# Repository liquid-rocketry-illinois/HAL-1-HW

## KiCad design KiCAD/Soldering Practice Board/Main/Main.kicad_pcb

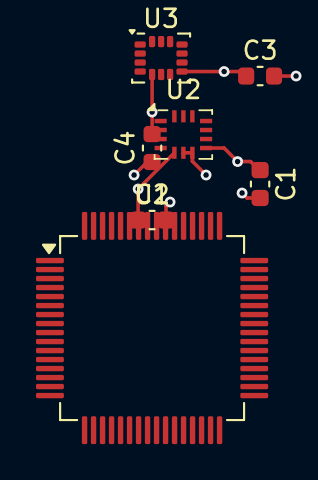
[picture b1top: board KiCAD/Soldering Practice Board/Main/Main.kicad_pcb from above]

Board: 2 copper layers, 7 parts (0 on the bottom side), 2 nets.

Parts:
C1, C2, C3, C4: 100n; C_0603_1608Metric
U1: STM32C071R8Tx; LQFP-64_10x10mm_P0.5mm
U2: BMI160; Bosch_LGA-14_3x2.5mm_P0.5mm
U3: LSM6DS3; LGA-14_3x2.5mm_P0.5mm_LayoutBorder3x4y

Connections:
+3V3: C1.1, C2.1, C3.1, C4.2, U1.7 (VREF+), U1.8 (VDD), U2.5 (VDDIO), U2.8 (VDD), U3.5 (VDDIO), U3.8 (VDD)
GND: C1.2, C2.2, C3.2, C4.1, U1.9 (VSS), U2.6 (GNDIO), U2.7 (GND), U3.2 (SDX), U3.3 (SCX), U3.6 (GND), U3.7 (GND)

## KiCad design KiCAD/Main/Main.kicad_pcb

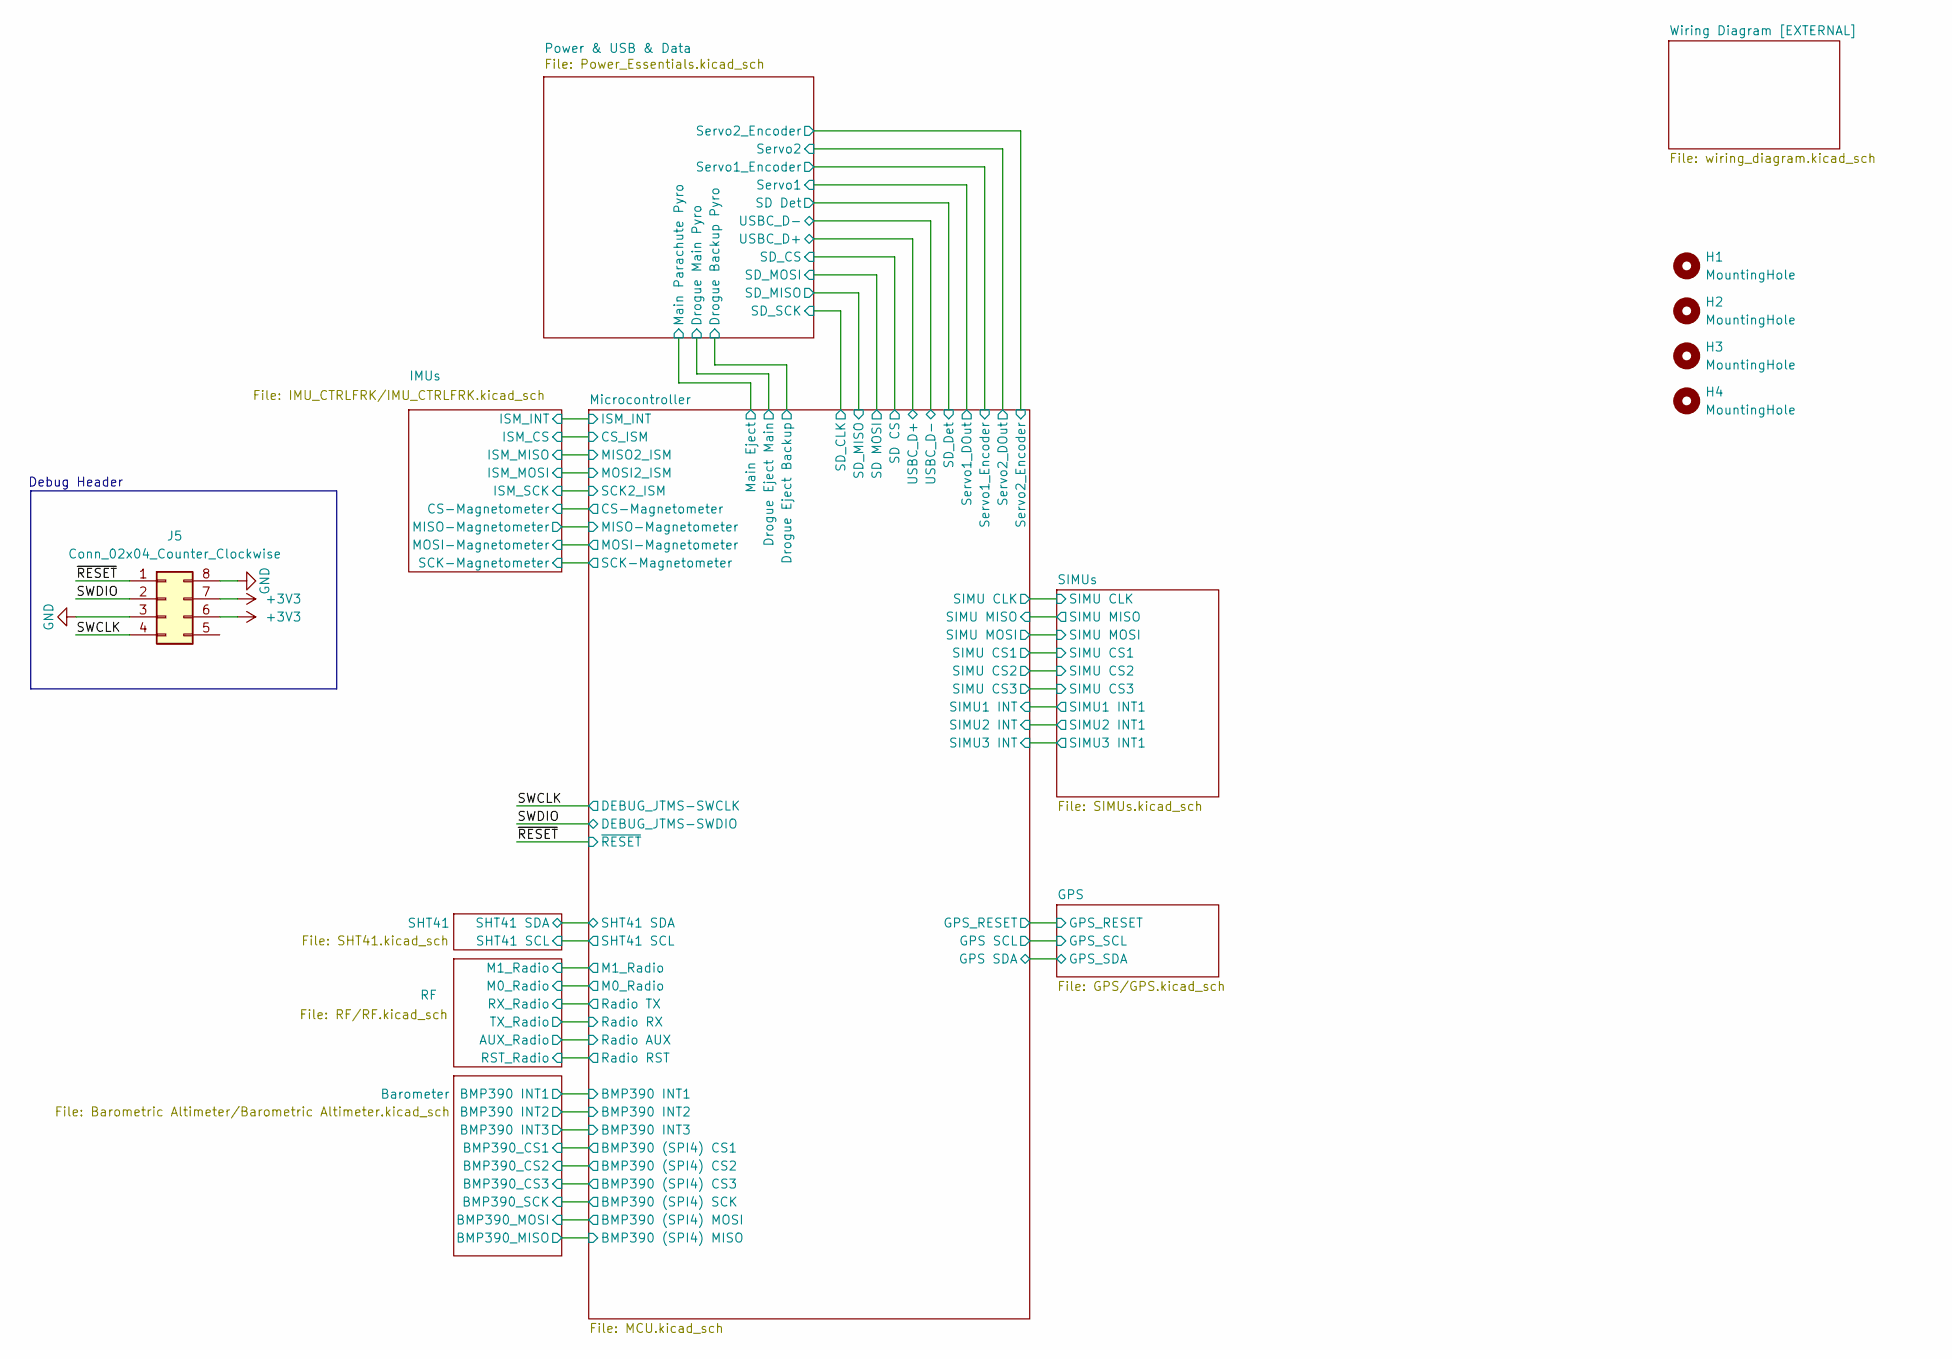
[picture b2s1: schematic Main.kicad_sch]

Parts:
H1, H2, H3, H4: MountingHole; MountingHole_3.2mm_M3
J5: Conn_02x04_Counter_Clockwise; PinHeader_2x04_P2.54mm_Vertical

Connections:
+3V3: J5.6, J5.7; also elsewhere on the board
/SWCLK: J5.4; also elsewhere on the board
/SWDIO: J5.2; also elsewhere on the board
/~RESET: J5.1; also elsewhere on the board
GND: J5.3, J5.8; also elsewhere on the board

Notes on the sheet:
Debug Header

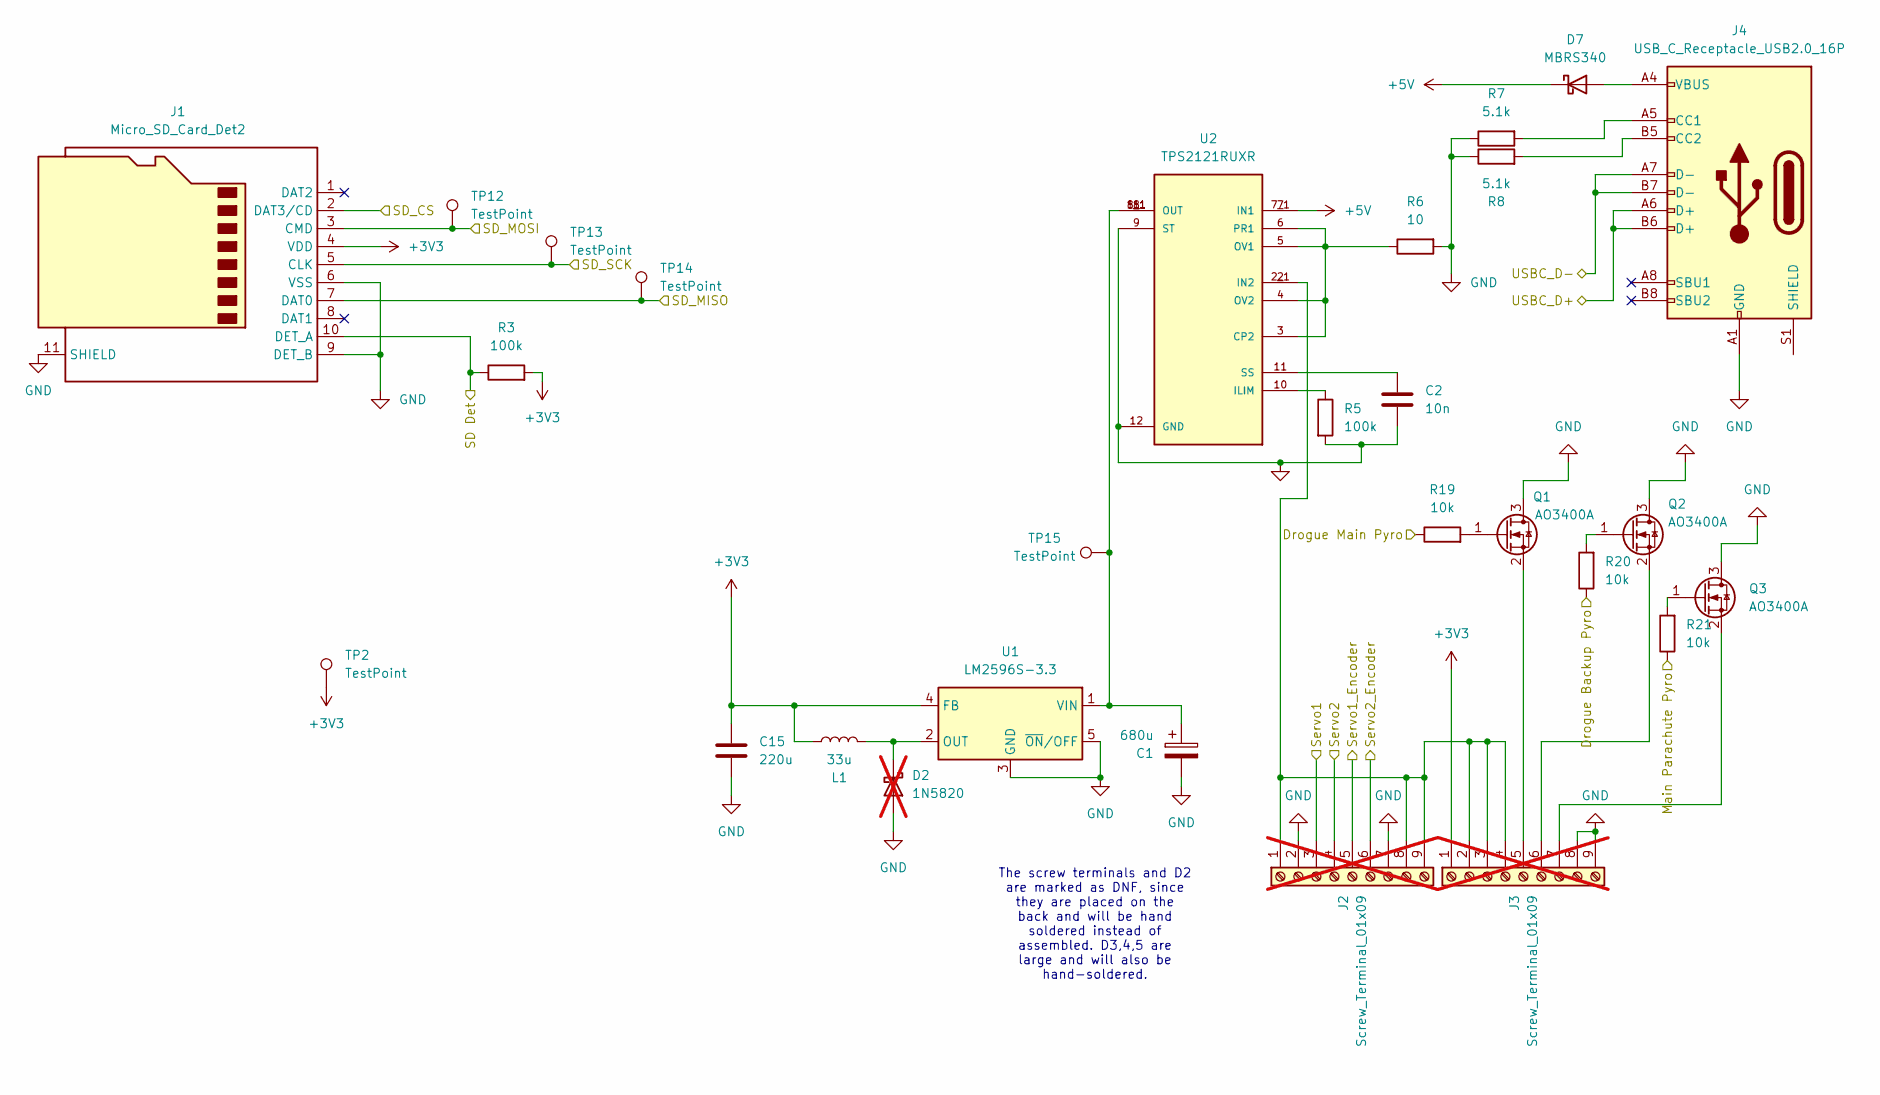
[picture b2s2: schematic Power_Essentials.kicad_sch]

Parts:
C1: 680u; CP_Elec_10x12.6
C2: 10n; C_0603_1608Metric
C15: 220u; C_1206_3216Metric
D2: 1N5820; D_DO-201AD_P15.24mm_Horizontal; not fitted
D7: MBRS340; D_SMC
J1: Micro_SD_Card_Det2; microSD_HC_Hirose_DM3AT-SF-PEJM5
J2, J3: Screw_Terminal_01x09; TerminalBlock_Phoenix_MKDS-1,5-9_1x09_P5.00mm_Horizontal; not fitted
J4: USB_C_Receptacle_USB2.0_16P; USB_C_Receptacle_HRO_TYPE-C-31-M-12
L1: 33u; L_SXN_SMDRI127
Q1, Q2, Q3: AO3400A; SOT-23
R3, R5: 100k; R_0603_1608Metric
R6: 10; R_0603_1608Metric
R7, R8: 5.1k; R_0603_1608Metric
R19, R20, R21: 10k; R_0603_1608Metric
TP2, TP12, TP13, TP14, TP15: TestPoint; TestPoint_Pad_D1.0mm
U1: LM2596S-3.3; TO-263-5_TabPin3
U2: TPS2121RUXR; Texas_VQFN-HR-12_2x2.5mm_P0.5mm_ThermalVias

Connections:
+3V3: C15.1, J1.4 (VDD), J3.1 (3V3_OUT), L1.1, R3.2, TP2.1, U1.4 (FB); also elsewhere on the board
+5V: D7.1 (K), U2.7 (IN1), U2.7_1 (IN1)
/Microcontroller/Drogue Eject Backup: R20.1; also elsewhere on the board
/Microcontroller/Drogue Eject Main: R19.1; also elsewhere on the board
/Microcontroller/Main Eject: R21.1; also elsewhere on the board
/Microcontroller/SD CS: J1.2 (DAT3/CD); also elsewhere on the board
/Microcontroller/SD MOSI: J1.3 (CMD), TP12.1; also elsewhere on the board
/Microcontroller/SD_CLK: J1.5 (CLK), TP13.1; also elsewhere on the board
/Microcontroller/SD_Det: J1.10 (DET_A), R3.1; also elsewhere on the board
/Microcontroller/SD_MISO: J1.7 (DAT0), TP14.1; also elsewhere on the board
/Microcontroller/Servo1_DOut: J2.3 (Servo1); also elsewhere on the board
/Microcontroller/Servo1_Encoder: J2.5 (Servo1_Encoder); also elsewhere on the board
/Microcontroller/Servo2_DOut: J2.4 (Servo2); also elsewhere on the board
/Microcontroller/Servo2_Encoder: J2.6 (Servo2_Encoder); also elsewhere on the board
/Microcontroller/USBC_D+: J4.A6 (D+), J4.B6 (D+); also elsewhere on the board
/Microcontroller/USBC_D-: J4.A7 (D-), J4.B7 (D-); also elsewhere on the board
GND: C1.2, C2.2, C15.2, D2.2 (A), J1.6 (VSS), J1.9 (DET_B), J1.11 (SHIELD), J2.2 (GND), J2.7 (MotorGND), J3.8, J3.9 (GND), J4.A1 (GND), J4.A12 (GND), J4.B1 (GND), J4.B12 (GND), Q1.3 (D), Q2.3 (D), Q3.3 (D), R5.2, R6.2, R7.1, R8.1, U1.3 (GND), U1.5 (~ON/OFF), U2.9 (ST), U2.12 (GND); also elsewhere on the board
unnamed: D2.1 (K), L1.2, U1.2 (OUT)
unnamed: D7.2 (A), J4.A4 (VBUS), J4.A9 (VBUS), J4.B4 (VBUS), J4.B9 (VBUS)
unnamed: J2.1 (7.4V_IN), J2.8 (MotorPwr1), J2.9 (MotorPwr2), J3.2 (Pyro_OUT_1), J3.3 (Pyro_OUT_2), J3.4 (Pyro_OUT_3), U2.2 (IN2), U2.2_1 (IN2)
unnamed: J3.6 (Drogue_Backup), Q2.2 (S)
unnamed: J3.5 (Drogue_Main), Q1.2 (S)
unnamed: J3.7 (Main_Parachute), Q3.2 (S)
unnamed: J4.A5 (CC1), R7.2
unnamed: J4.B5 (CC2), R8.2
unnamed: Q1.1 (G), R19.2
unnamed: Q2.1 (G), R20.2
unnamed: Q3.1 (G), R21.2
unnamed: C1.1, TP15.1, U1.1 (VIN), U2.1 (OUT), U2.1_1 (OUT), U2.8 (OUT), U2.8_1 (OUT)
unnamed: R6.1, U2.3 (CP2), U2.4 (OV2), U2.5 (OV1), U2.6 (PR1)
unnamed: R5.1, U2.10 (ILIM)
unnamed: C2.1, U2.11 (SS)

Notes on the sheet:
The screw terminals and D2 are marked as DNF, since they are placed on the back and will be hand soldered instead of assembled. D3,4,5 are large and will also be hand-soldered.

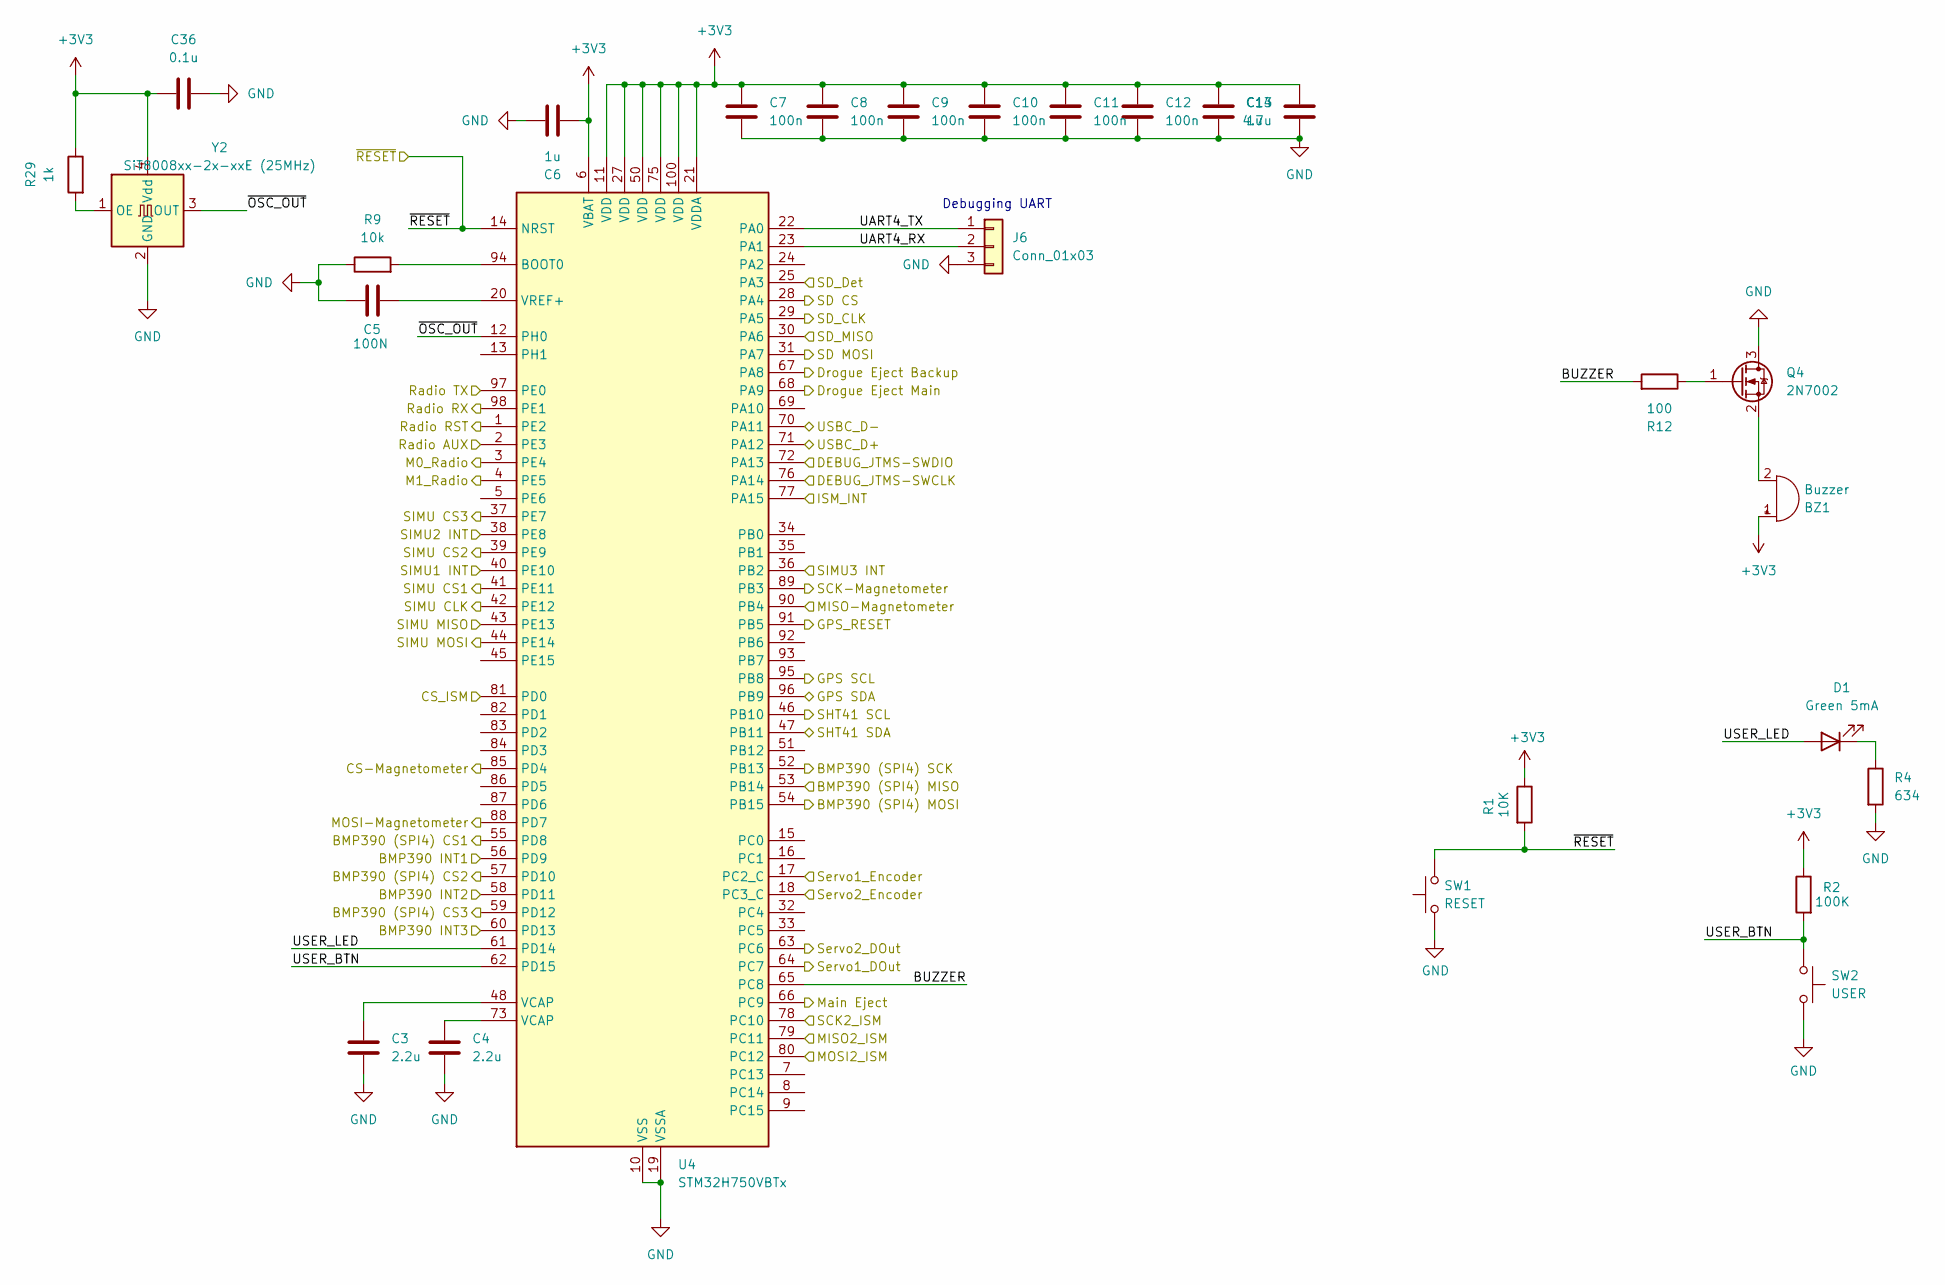
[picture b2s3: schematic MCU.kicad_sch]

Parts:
BZ1: Buzzer; Buzzer_12x9.5RM7.6
C3, C4: 2.2u; C_0603_1608Metric
C5: 100N; C_0603_1608Metric
C6, C13: 1u; C_0603_1608Metric
C7, C8, C9, C10, C11, C12: 100n; C_0603_1608Metric
C14: 4.7u; C_0603_1608Metric
C36: 0.1u; C_0603_1608Metric
D1: Green 5mA; LED_0603_1608Metric
J6: Conn_01x03; PinHeader_1x03_P2.54mm_Vertical
Q4: 2N7002; SOT-23
R1: 10K; R_0603_1608Metric
R2: 100K; R_0603_1608Metric
R4: 634; R_0603_1608Metric
R9: 10k; R_0603_1608Metric
R12: 100; R_0603_1608Metric
R29: 1k; R_0603_1608Metric
SW1: RESET; SW_Push_1P1T_NO_Vertical_Wuerth_434133025816
SW2: USER; SW_Push_1P1T_NO_Vertical_Wuerth_434133025816
U4: STM32H750VBTx; LQFP-100_14x14mm_P0.5mm
Y2: SiT8008xx-2x-xxE (25MHz); Oscillator_SMD_SiT_PQFN-4Pin_3.2x2.5mm

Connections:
+3V3: BZ1.1 (+), C6.2, C7.1, C8.1, C9.1, C10.1, C11.1, C12.1, C13.1, C14.1, C36.2, R1.1, R2.1, R29.1, U4.6 (VBAT), U4.11 (VDD), U4.21 (VDDA), U4.27 (VDD), U4.50 (VDD), U4.75 (VDD), U4.100 (VDD), Y2.4 (Vdd); also elsewhere on the board
/Barometer/BMP390 INT1: U4.56 (PD9); also elsewhere on the board
/Barometer/BMP390 INT2: U4.58 (PD11); also elsewhere on the board
/Barometer/BMP390 INT3: U4.60 (PD13); also elsewhere on the board
/Barometer/BMP390_CS1: U4.55 (PD8); also elsewhere on the board
/Barometer/BMP390_CS2: U4.57 (PD10); also elsewhere on the board
/Barometer/BMP390_CS3: U4.59 (PD12); also elsewhere on the board
/Barometer/BMP390_MISO: U4.53 (PB14); also elsewhere on the board
/Barometer/BMP390_MOSI: U4.54 (PB15); also elsewhere on the board
/Barometer/BMP390_SCK: U4.52 (PB13); also elsewhere on the board
/GPS/GPS_RESET: U4.91 (PB5); also elsewhere on the board
/GPS/GPS_SCL: U4.95 (PB8); also elsewhere on the board
/GPS/GPS_SDA: U4.96 (PB9); also elsewhere on the board
/IMUs/CS-Magnetometer: U4.85 (PD4); also elsewhere on the board
/IMUs/ISM_CS: U4.81 (PD0); also elsewhere on the board
/IMUs/ISM_INT: U4.77 (PA15); also elsewhere on the board
/IMUs/ISM_MISO: U4.79 (PC11); also elsewhere on the board
/IMUs/ISM_MOSI: U4.80 (PC12); also elsewhere on the board
/IMUs/ISM_SCK: U4.78 (PC10); also elsewhere on the board
/IMUs/MISO-Magnetometer: U4.90 (PB4); also elsewhere on the board
/IMUs/MOSI-Magnetometer: U4.88 (PD7); also elsewhere on the board
/IMUs/SCK-Magnetometer: U4.89 (PB3); also elsewhere on the board
/Microcontroller/BUZZER: R12.2, U4.65 (PC8)
/Microcontroller/Drogue Eject Backup: U4.67 (PA8); also elsewhere on the board
/Microcontroller/Drogue Eject Main: U4.68 (PA9); also elsewhere on the board
/Microcontroller/M0_Radio: U4.3 (PE4); also elsewhere on the board
/Microcontroller/M1_Radio: U4.4 (PE5); also elsewhere on the board
/Microcontroller/Main Eject: U4.66 (PC9); also elsewhere on the board
/Microcontroller/Radio AUX: U4.2 (PE3); also elsewhere on the board
/Microcontroller/Radio RST: U4.1 (PE2); also elsewhere on the board
/Microcontroller/Radio RX: U4.98 (PE1); also elsewhere on the board
/Microcontroller/Radio TX: U4.97 (PE0); also elsewhere on the board
/Microcontroller/SD CS: U4.28 (PA4); also elsewhere on the board
/Microcontroller/SD MOSI: U4.31 (PA7); also elsewhere on the board
/Microcontroller/SD_CLK: U4.29 (PA5); also elsewhere on the board
/Microcontroller/SD_Det: U4.25 (PA3); also elsewhere on the board
/Microcontroller/SD_MISO: U4.30 (PA6); also elsewhere on the board
/Microcontroller/SHT41 SCL: U4.46 (PB10); also elsewhere on the board
/Microcontroller/SHT41 SDA: U4.47 (PB11); also elsewhere on the board
/Microcontroller/SIMU1 INT: U4.40 (PE10); also elsewhere on the board
/Microcontroller/SIMU2 INT: U4.38 (PE8); also elsewhere on the board
/Microcontroller/SIMU3 INT: U4.36 (PB2); also elsewhere on the board
/Microcontroller/SIMU CLK: U4.42 (PE12); also elsewhere on the board
/Microcontroller/SIMU CS1: U4.41 (PE11); also elsewhere on the board
/Microcontroller/SIMU CS2: U4.39 (PE9); also elsewhere on the board
/Microcontroller/SIMU CS3: U4.37 (PE7); also elsewhere on the board
/Microcontroller/SIMU MISO: U4.43 (PE13); also elsewhere on the board
/Microcontroller/SIMU MOSI: U4.44 (PE14); also elsewhere on the board
/Microcontroller/Servo1_DOut: U4.64 (PC7); also elsewhere on the board
/Microcontroller/Servo1_Encoder: U4.17 (PC2_C); also elsewhere on the board
/Microcontroller/Servo2_DOut: U4.63 (PC6); also elsewhere on the board
/Microcontroller/Servo2_Encoder: U4.18 (PC3_C); also elsewhere on the board
/Microcontroller/UART4_RX: J6.2, U4.23 (PA1)
/Microcontroller/UART4_TX: J6.1, U4.22 (PA0)
/Microcontroller/USBC_D+: U4.71 (PA12); also elsewhere on the board
/Microcontroller/USBC_D-: U4.70 (PA11); also elsewhere on the board
/Microcontroller/USER_BTN: R2.2, SW2.2, U4.62 (PD15)
/Microcontroller/USER_LED: D1.2 (A), U4.61 (PD14)
/Microcontroller/~OSC_OUT: U4.12 (PH0), Y2.3 (OUT)
/SWCLK: U4.76 (PA14); also elsewhere on the board
/SWDIO: U4.72 (PA13); also elsewhere on the board
/~RESET: R1.2, SW1.2, U4.14 (NRST); also elsewhere on the board
GND: C3.2, C4.2, C5.1, C6.1, C7.2, C8.2, C9.2, C10.2, C11.2, C12.2, C13.2, C14.2, C36.1, J6.3, Q4.3 (D), R4.2, R9.1, SW1.1, SW2.1, U4.10 (VSS), U4.19 (VSSA), U4.26 (VSS), U4.49 (VSS), U4.74 (VSS), U4.99 (VSS), Y2.2 (GND); also elsewhere on the board
unnamed: BZ1.2 (-), Q4.2 (S)
unnamed: C3.1, U4.48 (VCAP)
unnamed: C4.1, U4.73 (VCAP)
unnamed: D1.1 (K), R4.1
unnamed: Q4.1 (G), R12.1
unnamed: R9.2, U4.94 (BOOT0)
unnamed: C5.2, U4.20 (VREF+)
unnamed: R29.2, Y2.1 (OE)

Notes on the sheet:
Debugging UART

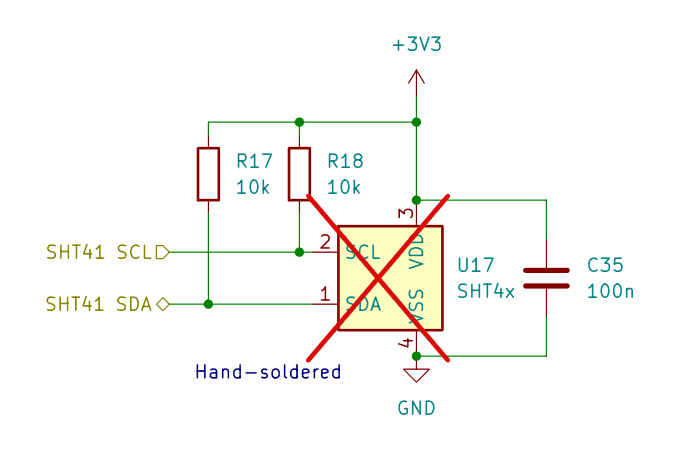
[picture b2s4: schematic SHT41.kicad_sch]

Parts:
C35: 100n; C_0603_1608Metric
R17, R18: 10k; R_0603_1608Metric
U17: SHT4x; Sensirion_DFN-4_1.5x1.5mm_P0.8mm_SHT4x_NoCentralPad; not fitted

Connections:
+3V3: C35.1, R17.1, R18.1, U17.3 (VDD); also elsewhere on the board
/Microcontroller/SHT41 SCL: R18.2, U17.2 (SCL); also elsewhere on the board
/Microcontroller/SHT41 SDA: R17.2, U17.1 (SDA); also elsewhere on the board
GND: C35.2, U17.4 (VSS); also elsewhere on the board

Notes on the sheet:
Hand-soldered

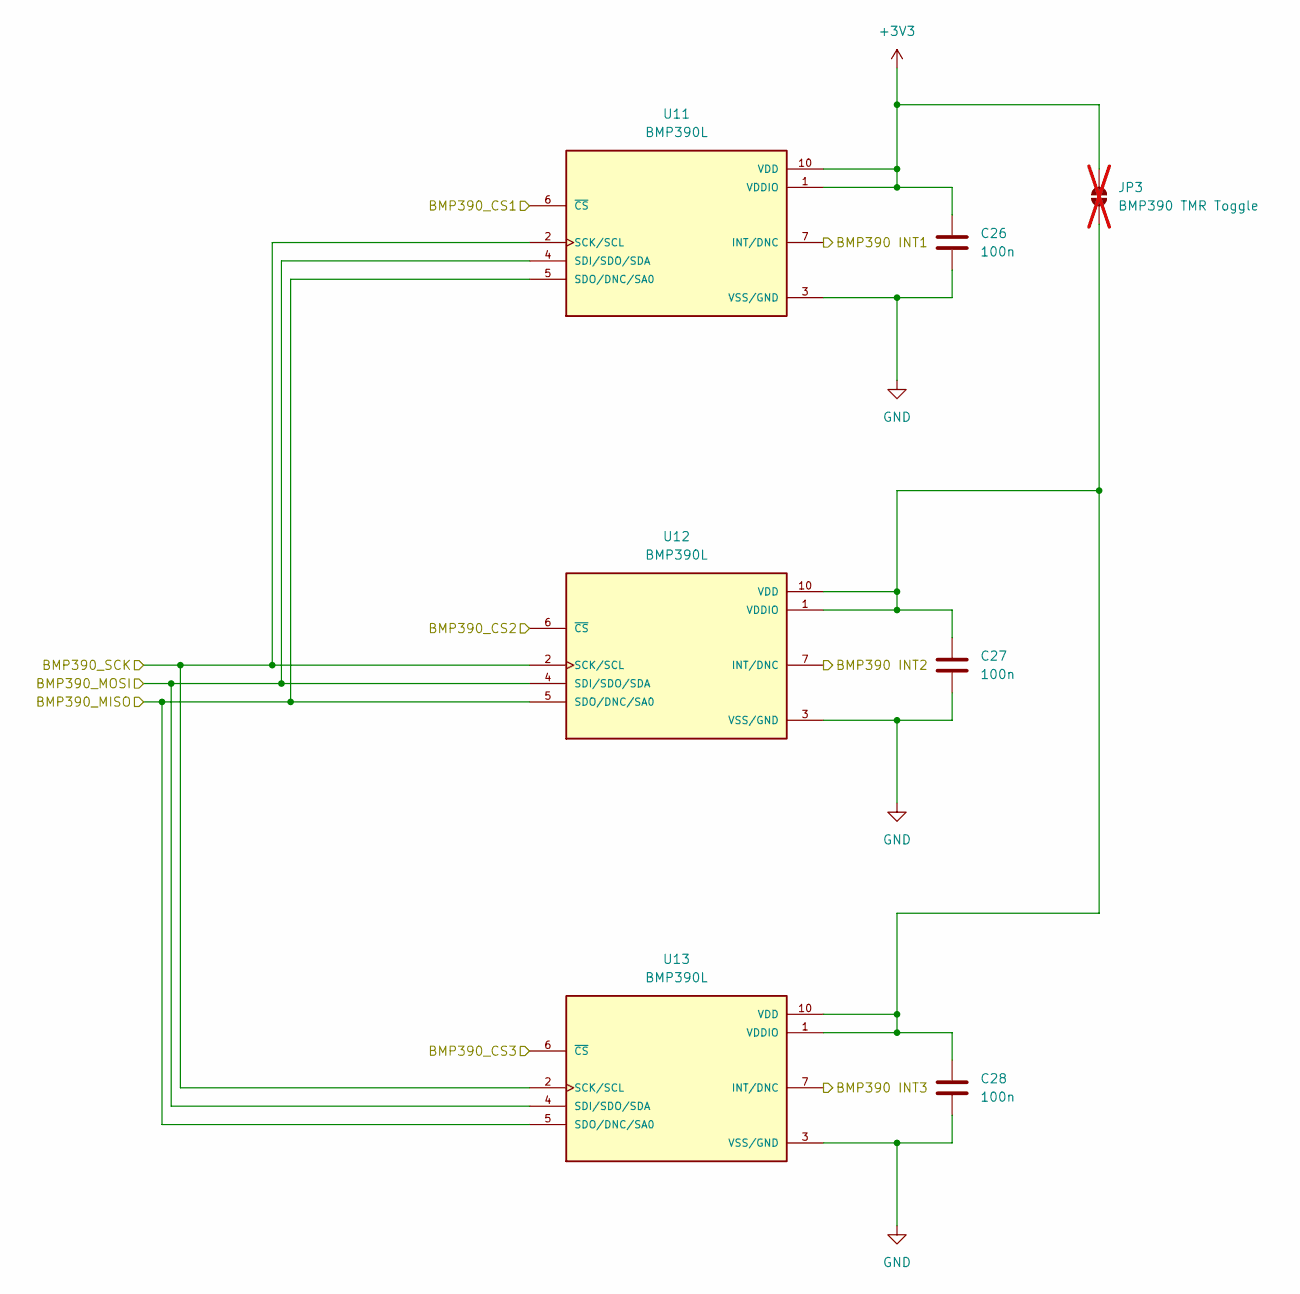
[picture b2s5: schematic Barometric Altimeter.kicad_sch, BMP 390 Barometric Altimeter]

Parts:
C26, C27, C28: 100n; C_0603_1608Metric
JP3: BMP390 TMR Toggle; SolderJumper-2_P1.3mm_Open_RoundedPad1.0x1.5mm; not fitted
U11, U12, U13: BMP390L; XDCR_BMP390L; PARTREV 1.7

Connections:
+3V3: C26.1, JP3.2 (B), U11.1 (VDDIO), U11.10 (VDD); also elsewhere on the board
/Barometer/BMP390 INT1: U11.7 (INT/DNC); also elsewhere on the board
/Barometer/BMP390 INT2: U12.7 (INT/DNC); also elsewhere on the board
/Barometer/BMP390 INT3: U13.7 (INT/DNC); also elsewhere on the board
/Barometer/BMP390_CS1: U11.6 (~CS); also elsewhere on the board
/Barometer/BMP390_CS2: U12.6 (~CS); also elsewhere on the board
/Barometer/BMP390_CS3: U13.6 (~CS); also elsewhere on the board
/Barometer/BMP390_MISO: U11.5 (SDO/DNC/SA0), U12.5 (SDO/DNC/SA0), U13.5 (SDO/DNC/SA0); also elsewhere on the board
/Barometer/BMP390_MOSI: U11.4 (SDI/SDO/SDA), U12.4 (SDI/SDO/SDA), U13.4 (SDI/SDO/SDA); also elsewhere on the board
/Barometer/BMP390_SCK: U11.2 (SCK/SCL), U12.2 (SCK/SCL), U13.2 (SCK/SCL); also elsewhere on the board
GND: C26.2, C27.2, C28.2, U11.3 (VSS/GND), U11.8 (VSS/GND), U11.9 (VSS/GND), U12.3 (VSS/GND), U12.8 (VSS/GND), U12.9 (VSS/GND), U13.3 (VSS/GND), U13.8 (VSS/GND), U13.9 (VSS/GND); also elsewhere on the board
unnamed: C27.1, C28.1, JP3.1 (A), U12.1 (VDDIO), U12.10 (VDD), U13.1 (VDDIO), U13.10 (VDD)

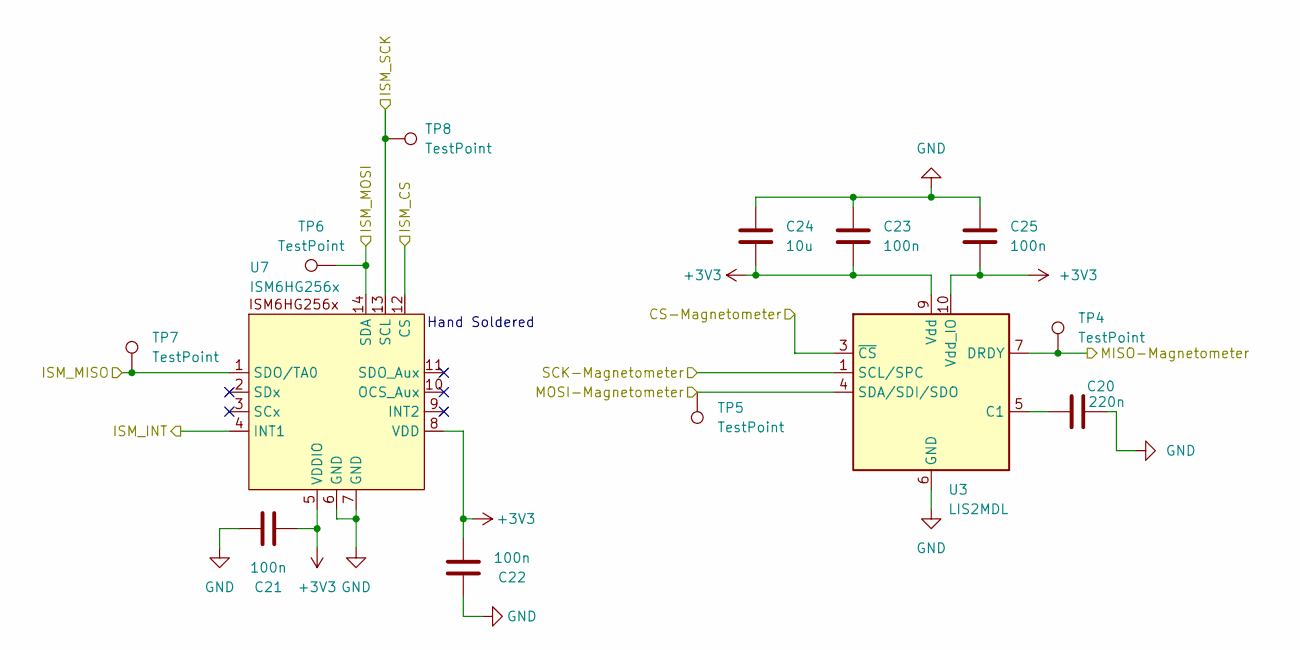
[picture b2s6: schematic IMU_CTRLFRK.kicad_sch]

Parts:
C20: 220n; C_0603_1608Metric
C21, C22, C23, C25: 100n; C_0603_1608Metric
C24: 10u; C_0603_1608Metric
TP4, TP5, TP6, TP7, TP8: TestPoint; TestPoint_Pad_D1.0mm
U3: LIS2MDL; LGA-12_2x2mm_P0.5mm
U7: ISM6HG256x; ISM6HG256XTR

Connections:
+3V3: C21.2, C22.2, C23.1, C24.1, C25.1, U3.9 (Vdd), U3.10 (Vdd_IO), U7.5 (VDDIO), U7.8 (VDD); also elsewhere on the board
/IMUs/CS-Magnetometer: U3.3 (~CS); also elsewhere on the board
/IMUs/ISM_CS: U7.12 (CS); also elsewhere on the board
/IMUs/ISM_INT: U7.4 (INT1); also elsewhere on the board
/IMUs/ISM_MISO: TP7.1, U7.1 (SDO/TA0); also elsewhere on the board
/IMUs/ISM_MOSI: TP6.1, U7.14 (SDA); also elsewhere on the board
/IMUs/ISM_SCK: TP8.1, U7.13 (SCL); also elsewhere on the board
/IMUs/MISO-Magnetometer: TP4.1, U3.7 (DRDY); also elsewhere on the board
/IMUs/MOSI-Magnetometer: TP5.1, U3.4 (SDA/SDI/SDO); also elsewhere on the board
/IMUs/SCK-Magnetometer: U3.1 (SCL/SPC); also elsewhere on the board
GND: C20.2, C21.1, C22.1, C23.2, C24.2, C25.2, U3.6 (GND), U3.8 (GND), U7.6 (GND), U7.7 (GND); also elsewhere on the board
unnamed: C20.1, U3.5 (C1)

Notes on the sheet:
Hand Soldered

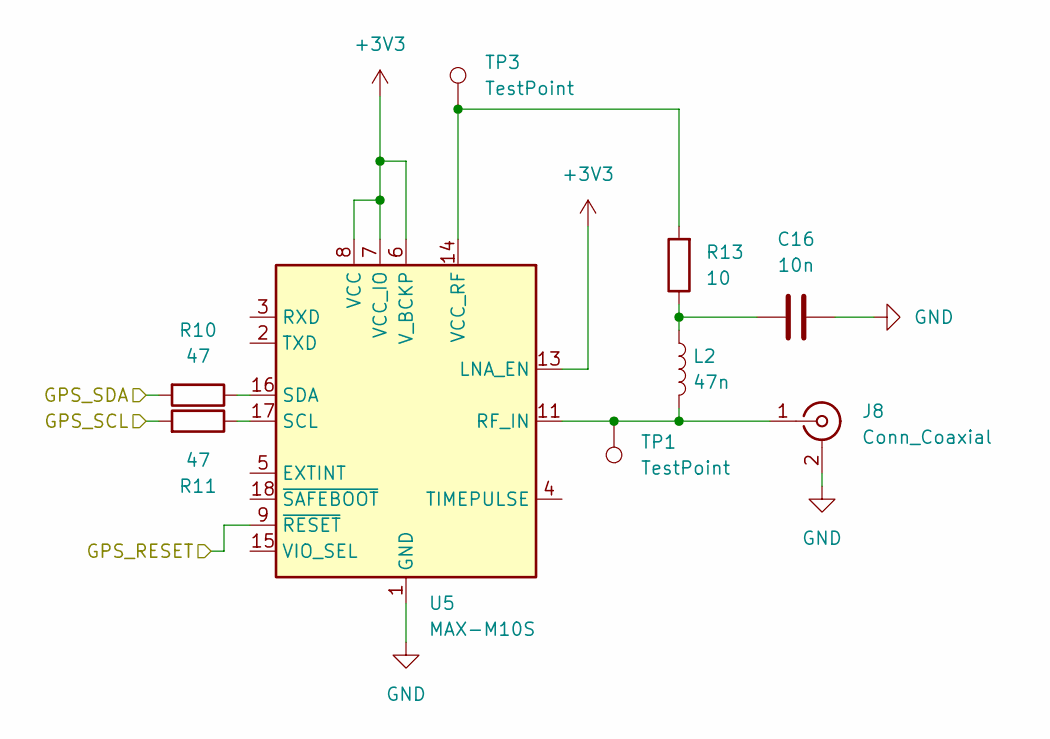
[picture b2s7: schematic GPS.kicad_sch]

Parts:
C16: 10n; C_0603_1608Metric
J8: Conn_Coaxial; U.FL_Molex_MCRF_73412-0110_Vertical
L2: 47n; L_0603_1608Metric
R10, R11: 47; R_0603_1608Metric
R13: 10; R_0603_1608Metric
TP1, TP3: TestPoint; TestPoint_Pad_D1.0mm
U5: MAX-M10S; ublox_MAX

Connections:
+3V3: U5.6 (V_BCKP), U5.7 (VCC_IO), U5.8 (VCC), U5.13 (LNA_EN); also elsewhere on the board
/GPS/GPS_RESET: U5.9 (~RESET); also elsewhere on the board
/GPS/GPS_SCL: R11.2; also elsewhere on the board
/GPS/GPS_SDA: R10.2; also elsewhere on the board
GND: C16.2, J8.2 (Ext), U5.1 (GND), U5.10 (GND), U5.12 (GND); also elsewhere on the board
unnamed: C16.1, L2.1, R13.1
unnamed: J8.1 (In), L2.2, TP1.1, U5.11 (RF_IN)
unnamed: R11.1, U5.17 (SCL)
unnamed: R10.1, U5.16 (SDA)
unnamed: R13.2, TP3.1, U5.14 (VCC_RF)

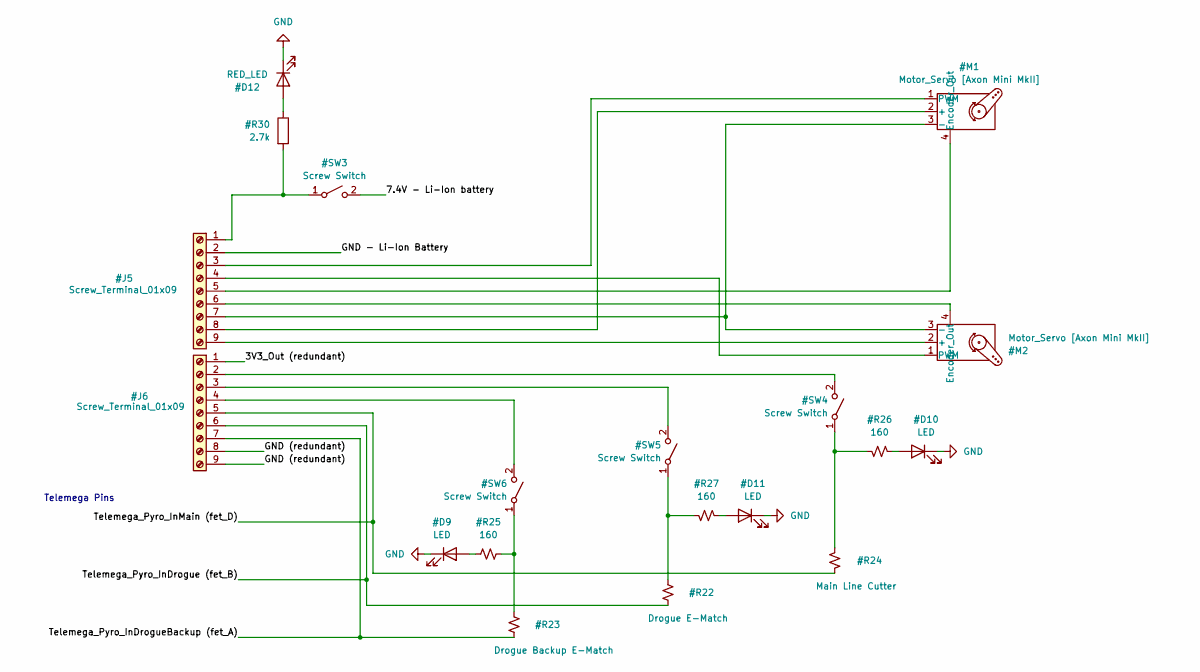
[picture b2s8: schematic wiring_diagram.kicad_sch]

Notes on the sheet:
Telemega Pins

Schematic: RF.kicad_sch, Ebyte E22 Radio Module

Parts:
C17, C19: 100n; C_0603_1608Metric
C18: 10n; C_0603_1608Metric
J9: Conn_Coaxial; U.FL_Molex_MCRF_73412-0110_Vertical
R16: 10k; R_0603_1608Metric
TP9, TP10, TP11: TestPoint; TestPoint_Pad_D1.0mm
U6: E22-900T22S

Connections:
+3V3: C17.1, C18.1, R16.1, U6.25 (VCC); also elsewhere on the board
/Microcontroller/M0_Radio: U6.20 (M0); also elsewhere on the board
/Microcontroller/M1_Radio: U6.21 (M1); also elsewhere on the board
/Microcontroller/Radio AUX: U6.24 (AUX); also elsewhere on the board
/Microcontroller/Radio RST: C19.1, R16.2, U6.1 (RESET); also elsewhere on the board
/Microcontroller/Radio RX: TP11.1, U6.23 (TX); also elsewhere on the board
/Microcontroller/Radio TX: TP10.1, U6.22 (RX); also elsewhere on the board
GND: C17.2, C18.2, C19.2, J9.2 (Ext), U6.2 (GND), U6.8 (GND), U6.11 (GND), U6.13 (GND), U6.14 (GND), U6.15 (GND), U6.16 (GND), U6.19 (GND), U6.26 (GND); also elsewhere on the board
unnamed: J9.1 (In), TP9.1, U6.12 (ANT)

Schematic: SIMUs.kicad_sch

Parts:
C29, C30, C31, C32, C33, C34: 100n; C_0603_1608Metric
JP2: BMI270 TMR Toggle; SolderJumper-2_P1.3mm_Open_RoundedPad1.0x1.5mm; not fitted
U8, U9, U10: BMI323

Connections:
+3V3: C29.1, C31.1, JP2.2 (B), U8.5 (VDDIO), U8.8 (VDD); also elsewhere on the board
/Microcontroller/SIMU1 INT: U8.4 (INT1); also elsewhere on the board
/Microcontroller/SIMU2 INT: U10.4 (INT1); also elsewhere on the board
/Microcontroller/SIMU3 INT: U9.4 (INT1); also elsewhere on the board
/Microcontroller/SIMU CLK: U8.13 (SCK), U9.13 (SCK), U10.13 (SCK); also elsewhere on the board
/Microcontroller/SIMU CS1: U8.12 (CS); also elsewhere on the board
/Microcontroller/SIMU CS2: U10.12 (CS); also elsewhere on the board
/Microcontroller/SIMU CS3: U9.12 (CS); also elsewhere on the board
/Microcontroller/SIMU MISO: U8.1 (MISO), U9.1 (MISO), U10.1 (MISO); also elsewhere on the board
/Microcontroller/SIMU MOSI: U8.14 (MOSI), U9.14 (MOSI), U10.14 (MOSI); also elsewhere on the board
GND: C29.2, C30.2, C31.2, C32.2, C33.2, C34.2, U8.6 (GNDIO), U8.7 (GND), U9.6 (GNDIO), U9.7 (GND), U10.6 (GNDIO), U10.7 (GND); also elsewhere on the board
unnamed: C30.1, C32.1, C33.1, C34.1, JP2.1 (A), U9.5 (VDDIO), U9.8 (VDD), U10.5 (VDDIO), U10.8 (VDD)
